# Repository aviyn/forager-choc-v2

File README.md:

# Forager Choc v2 / 19 mm

A fork of [Forager](https://github.com/carrefinho/forager) by [carrefinho](https://github.com/carrefinho), a Voyager-inspired 34-key low-profile wireless split keyboard powered by ZMK. This fork reworks the PCB for **Choc v2 hotswap switches at 19 × 19 mm spacing** (each half is about 8 mm wider and 6 mm taller) and adds, on each half:

- a power switch (Alps SSSS811101)
- an optional reset button (Panasonic EVQ-PUC02K)
- three SK6812MINI-E status LEDs behind a P-FET power switch

> [!WARNING]
> This fork has not been built yet. The first PCBs have just been ordered, so nothing here is tested on real hardware. Build it at your own risk.

The schematic and board are done, and the Gerbers in [`forager-pcb/GERBER-forager-pcb.zip`](/forager-pcb/GERBER-forager-pcb.zip) are generated from the current board. A new case for the left half is designed (see below). The firmware, including the status LEDs, is in [forager-choc-v2-zmk](https://github.com/aviyn/forager-choc-v2-zmk). The build guide has not been updated yet and still describes the original design. See [the full list of changes](/docs/changes.md).

Photos and design notes for the original Choc v1 Forager are in the [original Forager gallery](/docs/original-gallery.md).

## Case (left half)

The new case was designed in Fusion for the 19 × 19 mm board. Printable STEP and STL files are in [`exports/case/`](/exports/case/). It has four parts:

- **Top plate:** Choc v2 cutouts, shallower switch-puller grooves, four countersunk M2 screw holes, and three 1.75 mm holes for the LED light pipes.
- **Base:** a 1 mm deeper shell (bottom at Z −7.6) that fits a **601230** LiPo between two filleted floor ribs. It also has:
  - five bevelled screw posts, with countersunk M2 holes from below;
  - a 13 × 6.5 mm USB-C pocket;
  - a wall opening and a larger insertion relief for the power slider;
  - XIAO reset pinholes on both sides of the USB, so the same design mirrors to the right half;
  - flush magnet pockets for the stand;
  - four recesses for 10 × 3 mm bump-on feet.
- **Stand:** a 12° magnetic tenting stand that follows the case outline. Its top has pockets that clear the case's feet, and its bottom has two foot recesses. With the stand attached, all six feet are coplanar, so the board sits flat without rocking.
- **Power slider cap:** a small cap for the power switch.

All outer edges have 2 mm fillets, matched between the case and the stand.

**Status LEDs:** each half has three SK6812MINI-E RGB LEDs at a 4.5 mm pitch, reverse-mounted on the PCB's top inner edge so they shine up through cutouts in the board. Three light pipes carry the light to the top surface. Each is a piece of translucent 1.75 mm 3D-printer filament, cut to the top plate's thickness (about 2.1 mm) and pressed flush into its hole. A P-FET turns the LEDs' supply off when they aren't in use, so they draw no power. They are driven from the XIAO, which can set each LED to its own colour. In the render the pipes are coloured blue, green and red only to show where the light comes out. The LED behaviour (battery gauge, layer colour, caps lock and connection status) is described in the [forager-choc-v2-zmk](https://github.com/aviyn/forager-choc-v2-zmk) README.

The STEP and STL files are in assembly coordinates, so turn the top plate and the stand over in the slicer before printing.

**Right half:** only left-half files are provided. The case is designed to be mirrorable, so mirror each part across X in your slicer to print the right half. The XIAO reset pinhole on the other side of the USB lines up with the right-hand XIAO once mirrored.

## Build Guide and Parts List

[Find the build guide here.](/docs/build-guide.md) It still describes the original Choc v1 build; the Choc v2 parts (power switch, reset button, status LEDs and the new case) are not covered yet.

## Firmware

The ZMK config for this fork is in **[forager-choc-v2-zmk](https://github.com/aviyn/forager-choc-v2-zmk)**. It builds `forager_left` (the central, with ZMK Studio over USB), `forager_right` and `settings_reset` with GitHub Actions, and drives the status LEDs with [zmk-ledstrip-status](https://github.com/aviyn/zmk-ledstrip-status). It started from [forager-zmk-dongle](https://github.com/aviyn/forager-zmk-dongle), without the dongle. The original [Forager ZMK module](https://github.com/carrefinho/forager-zmk-module) by carrefinho is for the original Choc v1 board.

## Credits

- [carrefinho/forager](https://github.com/carrefinho/forager): the original Forager keyboard, PCB, case and firmware that this fork is based on
- [ZSA Voyager](https://www.zsa.io/voyager): overall layout & aesthetics
- [GEIGEIGEIST/TOTEM](https://github.com/GEIGEIGEIST/TOTEM): XIAO PCB footprint and general placement
- [ebastler/marbastlib](https://github.com/ebastler/marbastlib): symbols and PCB footprints
- [caksoylar/zmk-rgbled-widget](https://github.com/caksoylar/zmk-rgbled-widget): RGB LED functionality

## License

The original Forager and this fork are released under the [CERN Open Hardware Licence Version 2 - Permissive](/LICENSE).

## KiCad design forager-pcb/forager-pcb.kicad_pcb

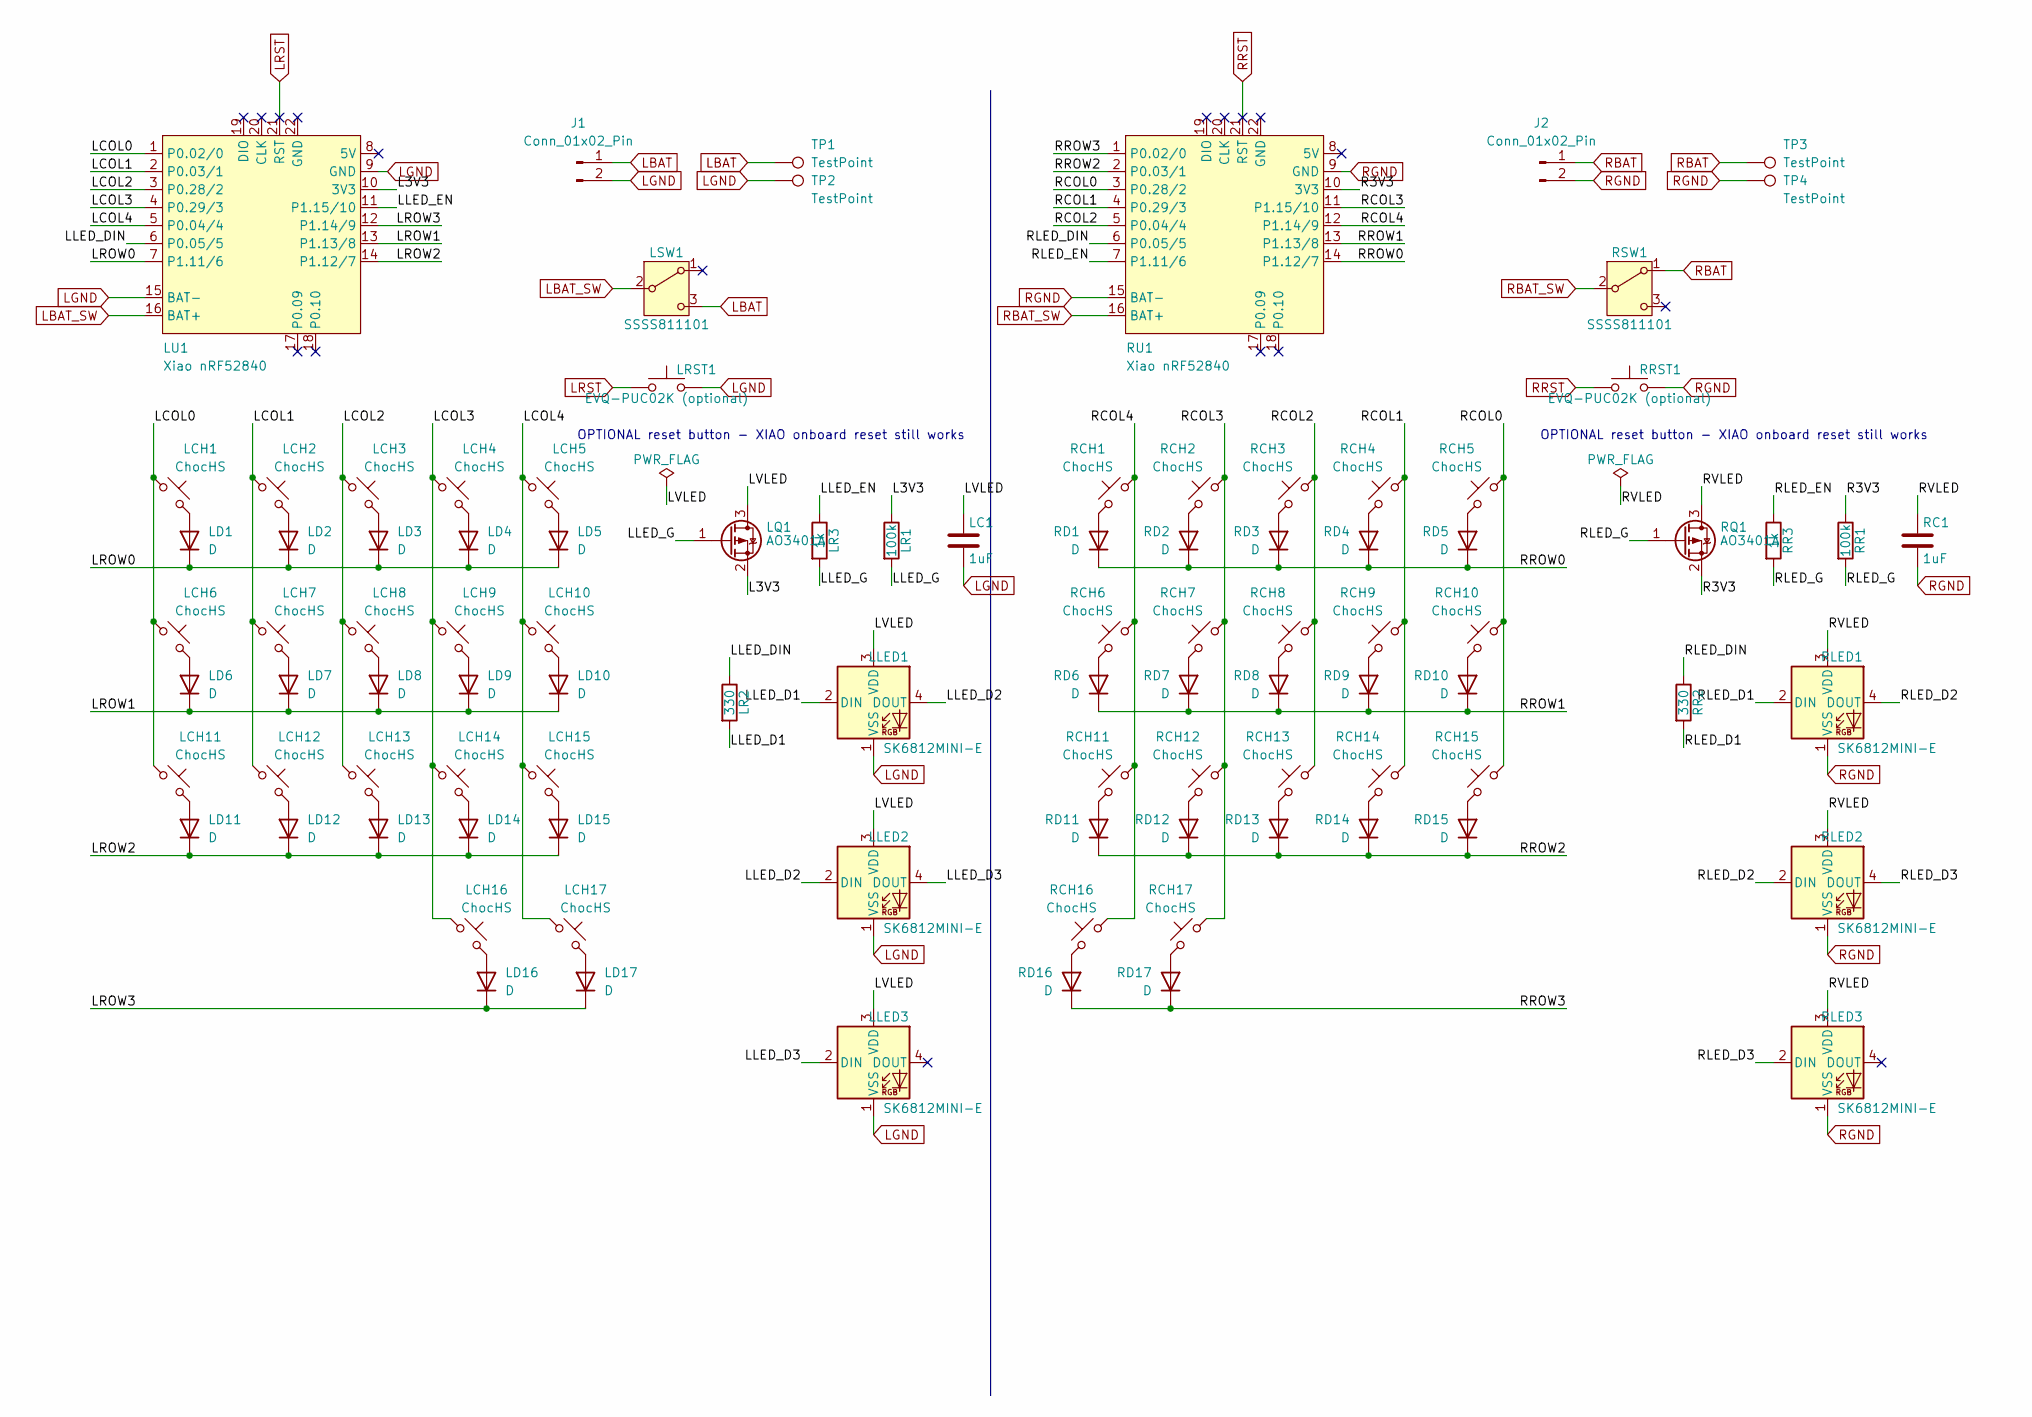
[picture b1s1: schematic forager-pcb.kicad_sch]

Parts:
J1, J2: Conn_01x02_Pin; JST_ACH_BM02B-ACHSS-GAN-ETF_1x02-1MP_P1.20mm_Vertical
LC1: 1uF; C_1206_3216Metric_Pad1.33x1.80mm_HandSolder; LCSC C1848
LCH1, LCH2, LCH3, LCH4, LCH5, LCH6, LCH7, LCH8, LCH9, LCH10, LCH11, LCH12, LCH13, LCH14, LCH15, LCH16, LCH17: ChocHS; SW_choc_v2_HS_CPG135001S30_1u_nopost
LD1, LD2, LD3, LD4, LD5, LD6, LD7, LD8, LD9, LD10, LD11, LD12, LD13, LD14, LD15, LD16, LD17: D; D_SOD-123
LLED1, LLED2, LLED3: SK6812MINI-E; LED_SK6812MINI-E_3.2x2.8mm_P1.5mm_ReverseMount; LCSC C5149201
LQ1: AO3401A; SOT-23; LCSC C347476
LR1: 100k; R_1206_3216Metric_Pad1.30x1.75mm_HandSolder; LCSC C17900
LR2: 330; R_1206_3216Metric_Pad1.30x1.75mm_HandSolder; LCSC C25374
LR3: 1k; R_1206_3216Metric_Pad1.30x1.75mm_HandSolder; LCSC C4410
LRST1: EVQ-PUC02K (optional); SW_Panasonic_EVQPUC02K
LSW1: SSSS811101; SW_SPDT_Alps_SSSS811101
LU1: Xiao nRF52840; xiao-ble-smd-cutout
RC1: 1uF; C_1206_3216Metric_Pad1.33x1.80mm_HandSolder; LCSC C1848
RCH1, RCH2, RCH3, RCH4, RCH5, RCH6, RCH7, RCH8, RCH9, RCH10, RCH11, RCH12, RCH13, RCH14, RCH15, RCH16, RCH17: ChocHS; SW_choc_v2_HS_CPG135001S30_1u_nopost
RD1, RD2, RD3, RD4, RD5, RD6, RD7, RD8, RD9, RD10, RD11, RD12, RD13, RD14, RD15, RD16, RD17: D; D_SOD-123
RLED1, RLED2, RLED3: SK6812MINI-E; LED_SK6812MINI-E_3.2x2.8mm_P1.5mm_ReverseMount; LCSC C5149201
RQ1: AO3401A; SOT-23; LCSC C347476
RR1: 100k; R_1206_3216Metric_Pad1.30x1.75mm_HandSolder; LCSC C17900
RR2: 330; R_1206_3216Metric_Pad1.30x1.75mm_HandSolder; LCSC C25374
RR3: 1k; R_1206_3216Metric_Pad1.30x1.75mm_HandSolder; LCSC C4410
RRST1: EVQ-PUC02K (optional); SW_Panasonic_EVQPUC02K
RSW1: SSSS811101; SW_SPDT_Alps_SSSS811101
RU1: Xiao nRF52840; xiao-ble-smd-cutout
TP1, TP2, TP3, TP4: TestPoint; TestPoint_Pad_D2.0mm

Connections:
/L3V3: LQ1.2 (S), LR1.1, LU1.10 (3V3)
/LCOL0: LCH1.1, LCH6.1, LCH11.1, LU1.1 (P0.02/0)
/LCOL1: LCH2.1, LCH7.1, LCH12.1, LU1.2 (P0.03/1)
/LCOL2: LCH3.1, LCH8.1, LCH13.1, LU1.3 (P0.28/2)
/LCOL3: LCH4.1, LCH9.1, LCH14.1, LCH16.1, LU1.4 (P0.29/3)
/LCOL4: LCH5.1, LCH10.1, LCH15.1, LCH17.1, LU1.5 (P0.04/4)
/LLED_D1: LLED1.2 (DIN), LR2.2
/LLED_D2: LLED1.4 (DOUT), LLED2.2 (DIN)
/LLED_D3: LLED2.4 (DOUT), LLED3.2 (DIN)
/LLED_DIN: LR2.1, LU1.6 (P0.05/5)
/LLED_EN: LR3.1, LU1.11 (P1.15/10)
/LLED_G: LQ1.1 (G), LR1.2, LR3.2
/LROW0: LD1.1 (K), LD2.1 (K), LD3.1 (K), LD4.1 (K), LD5.1 (K), LU1.7 (P1.11/6)
/LROW1: LD6.1 (K), LD7.1 (K), LD8.1 (K), LD9.1 (K), LD10.1 (K), LU1.13 (P1.13/8)
/LROW2: LD11.1 (K), LD12.1 (K), LD13.1 (K), LD14.1 (K), LD15.1 (K), LU1.14 (P1.12/7)
/LROW3: LD16.1 (K), LD17.1 (K), LU1.12 (P1.14/9)
/LVLED: LC1.1, LLED1.3 (VDD), LLED2.3 (VDD), LLED3.3 (VDD), LQ1.3 (D)
/R3V3: RQ1.2 (S), RR1.1, RU1.10 (3V3)
/RCOL0: RCH5.1, RCH10.1, RCH15.1, RU1.3 (P0.28/2)
/RCOL1: RCH4.1, RCH9.1, RCH14.1, RU1.4 (P0.29/3)
/RCOL2: RCH3.1, RCH8.1, RCH13.1, RU1.5 (P0.04/4)
/RCOL3: RCH2.1, RCH7.1, RCH12.1, RCH17.1, RU1.11 (P1.15/10)
/RCOL4: RCH1.1, RCH6.1, RCH11.1, RCH16.1, RU1.12 (P1.14/9)
/RLED_D1: RLED1.2 (DIN), RR2.2
/RLED_D2: RLED1.4 (DOUT), RLED2.2 (DIN)
/RLED_D3: RLED2.4 (DOUT), RLED3.2 (DIN)
/RLED_DIN: RR2.1, RU1.6 (P0.05/5)
/RLED_EN: RR3.1, RU1.7 (P1.11/6)
/RLED_G: RQ1.1 (G), RR1.2, RR3.2
/RROW0: RD1.1 (K), RD2.1 (K), RD3.1 (K), RD4.1 (K), RD5.1 (K), RU1.14 (P1.12/7)
/RROW1: RD6.1 (K), RD7.1 (K), RD8.1 (K), RD9.1 (K), RD10.1 (K), RU1.13 (P1.13/8)
/RROW2: RD11.1 (K), RD12.1 (K), RD13.1 (K), RD14.1 (K), RD15.1 (K), RU1.2 (P0.03/1)
/RROW3: RD16.1 (K), RD17.1 (K), RU1.1 (P0.02/0)
/RVLED: RC1.1, RLED1.3 (VDD), RLED2.3 (VDD), RLED3.3 (VDD), RQ1.3 (D)
LBAT: J1.1, LSW1.3 (C), TP1.1 (1_1)
LBAT_SW: LSW1.2 (B), LU1.16 (BAT+)
LGND: J1.2, LC1.2, LLED1.1 (VSS), LLED2.1 (VSS), LLED3.1 (VSS), LRST1.2, LU1.9 (GND), LU1.15 (BAT-), TP2.1 (1_1)
LRST: LRST1.1, LU1.21 (RST)
unnamed: LCH1.2, LD1.2 (A)
unnamed: LCH2.2, LD2.2 (A)
unnamed: LCH3.2, LD3.2 (A)
unnamed: LCH4.2, LD4.2 (A)
unnamed: LCH5.2, LD5.2 (A)
unnamed: LCH6.2, LD6.2 (A)
unnamed: LCH7.2, LD7.2 (A)
unnamed: LCH8.2, LD8.2 (A)
unnamed: LCH9.2, LD9.2 (A)
unnamed: LCH10.2, LD10.2 (A)
unnamed: LCH11.2, LD11.2 (A)
unnamed: LCH12.2, LD12.2 (A)
unnamed: LCH13.2, LD13.2 (A)
unnamed: LCH14.2, LD14.2 (A)
unnamed: LCH15.2, LD15.2 (A)
unnamed: LCH16.2, LD16.2 (A)
unnamed: LCH17.2, LD17.2 (A)
unnamed: RCH1.2, RD1.2 (A)
unnamed: RCH2.2, RD2.2 (A)
unnamed: RCH3.2, RD3.2 (A)
unnamed: RCH4.2, RD4.2 (A)
unnamed: RCH5.2, RD5.2 (A)
unnamed: RCH6.2, RD6.2 (A)
unnamed: RCH7.2, RD7.2 (A)
unnamed: RCH8.2, RD8.2 (A)
unnamed: RCH9.2, RD9.2 (A)
unnamed: RCH10.2, RD10.2 (A)
unnamed: RCH11.2, RD11.2 (A)
unnamed: RCH12.2, RD12.2 (A)
unnamed: RCH13.2, RD13.2 (A)
unnamed: RCH14.2, RD14.2 (A)
unnamed: RCH15.2, RD15.2 (A)
unnamed: RCH16.2, RD16.2 (A)
unnamed: RCH17.2, RD17.2 (A)
RBAT: J2.1, RSW1.1 (A), TP3.1 (1_1)
RBAT_SW: RSW1.2 (B), RU1.16 (BAT+)
RGND: J2.2, RC1.2, RLED1.1 (VSS), RLED2.1 (VSS), RLED3.1 (VSS), RRST1.2, RU1.9 (GND), RU1.15 (BAT-), TP4.1 (1_1)
RRST: RRST1.1, RU1.21 (RST)

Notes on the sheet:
OPTIONAL reset button - XIAO onboard reset still works

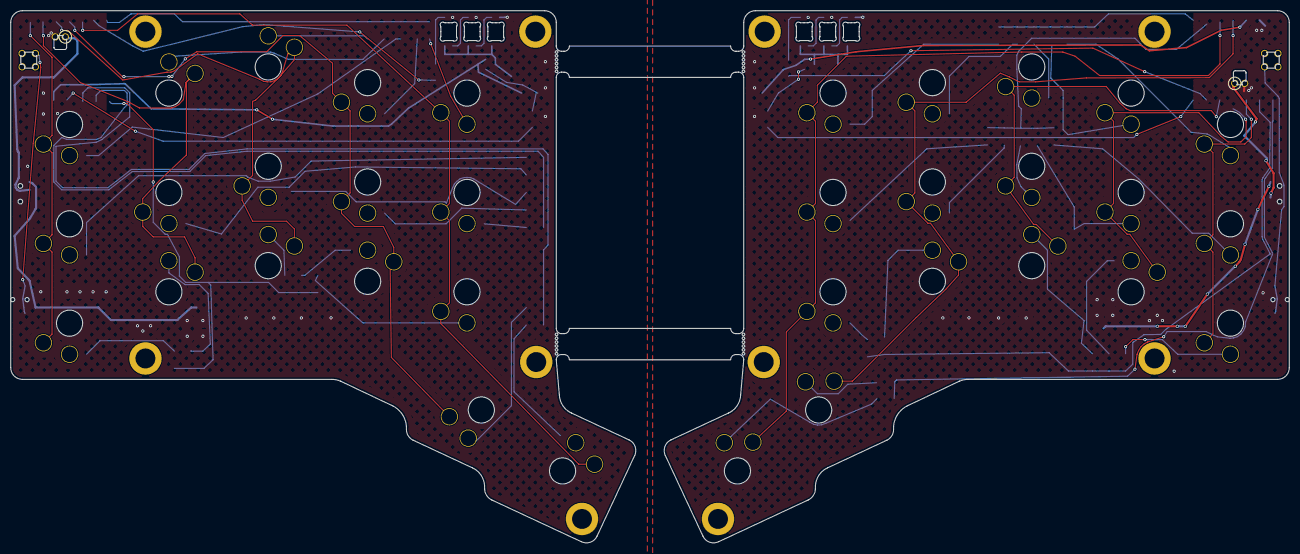
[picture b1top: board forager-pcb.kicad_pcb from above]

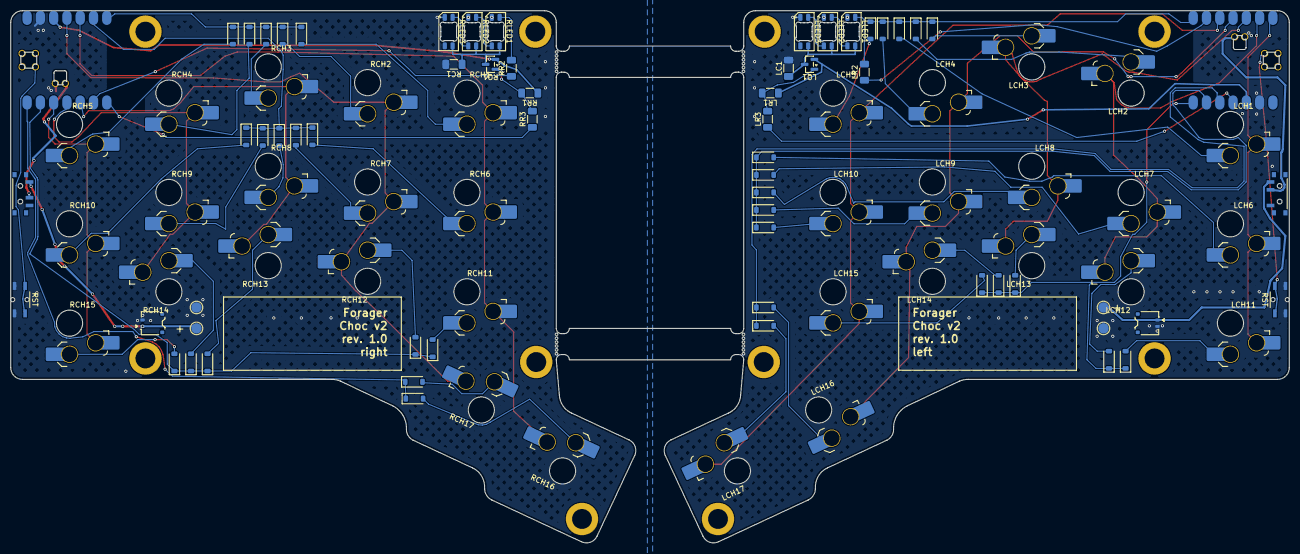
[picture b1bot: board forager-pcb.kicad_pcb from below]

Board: 2 copper layers, 244.5 x 101.8 mm, 96 parts (96 on the bottom side), 76 nets.
